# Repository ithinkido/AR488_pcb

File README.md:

# AR488_pcb
 Kicad Files for the AR488 GP-IB adapter with files for both the Pro MIcro and Nano MCU.

Silkcreen and solder mask to help with parts rotation. 

Files are avalible for single , 5x pannelization versions as well as 10x version which does not have mounting holes on the PCB. All designs fit in the 100x100mm size limit of most of the PSB manufactures.

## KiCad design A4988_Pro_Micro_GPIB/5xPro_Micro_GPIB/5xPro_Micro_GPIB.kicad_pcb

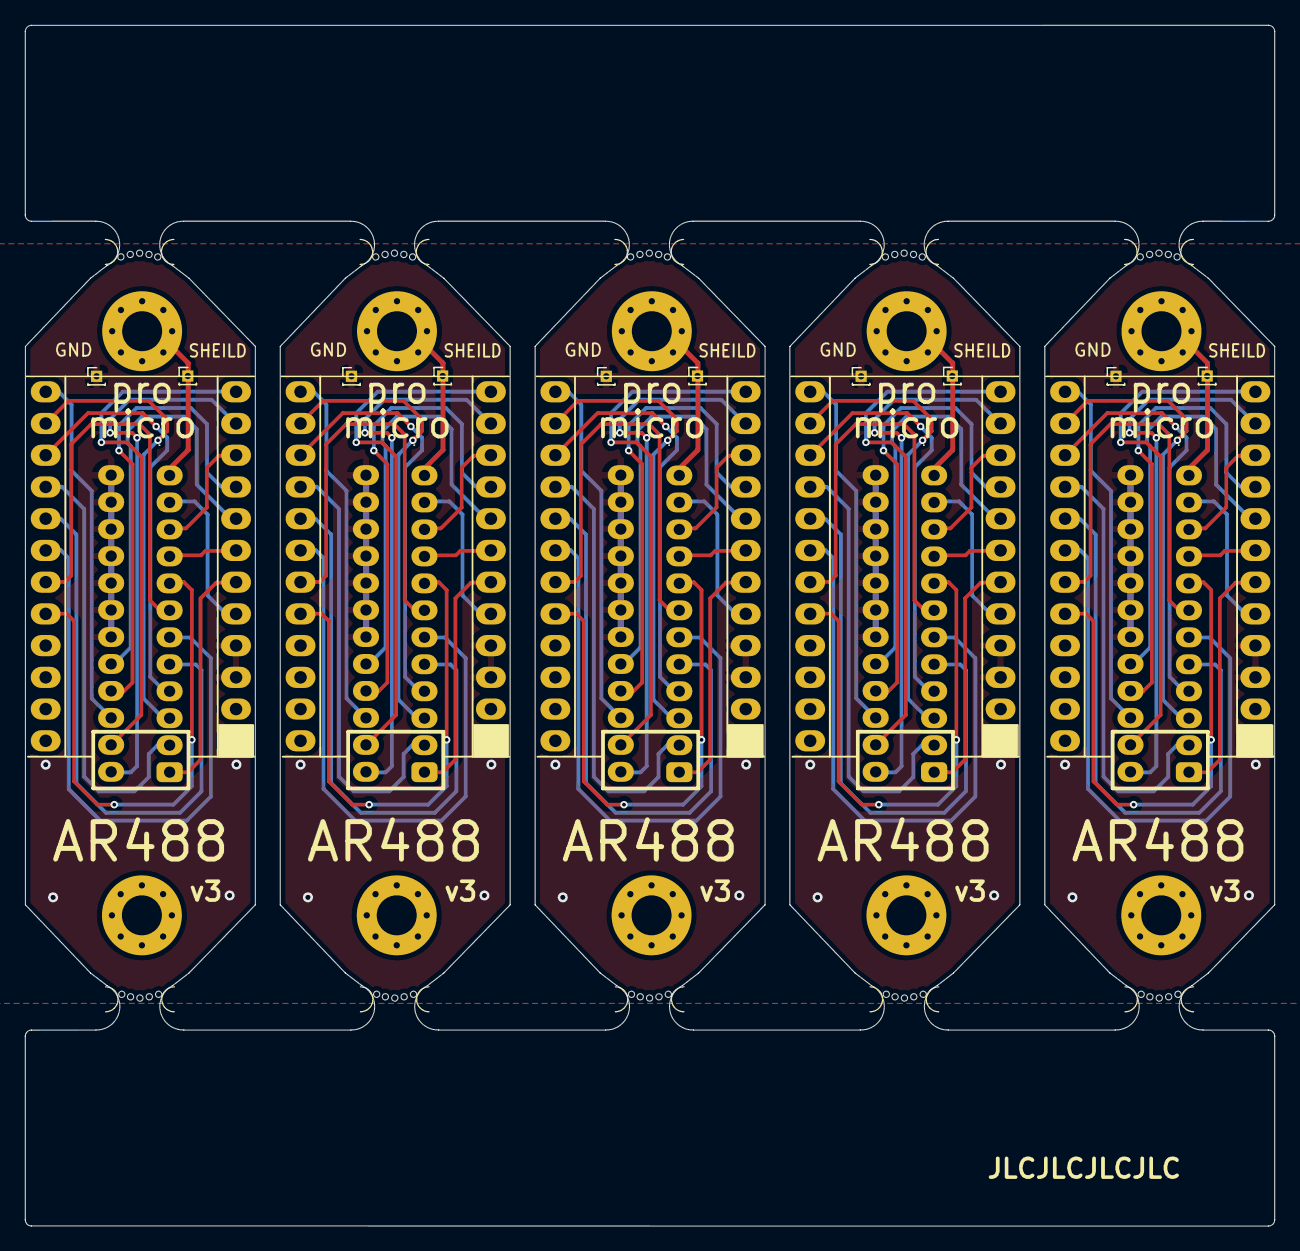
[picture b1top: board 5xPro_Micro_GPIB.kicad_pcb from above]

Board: 2 copper layers, 100.0 x 96.1 mm, 30 parts (0 on the bottom side), 18 nets.

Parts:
J1, J4, J7, J10, J13: Centronics_24p; Centronics24p
J2, J5, J8, J11, J14: GND; PinHeader_1x01_P1.00mm_Vertical
J3, J6, J9, J12, J15: SHIELD; PinHeader_1x01_P1.00mm_Vertical
U1, U2, U3, U4, U5: Pro_Micro_32u4; ProMicro-EnforcedTop
mouse-bite-2mm-slot, mouse-bite-2mm-slot1, mouse-bite-2mm-slot2, mouse-bite-2mm-slot3, mouse-bite-2mm-slot4, mouse-bite-2mm-slot5, mouse-bite-2mm-slot6, mouse-bite-2mm-slot7, mouse-bite-2mm-slot8, mouse-bite-2mm-slot#2: VAL**; mouse-bite-single-side_curve

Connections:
GND: J1.18, J1.19, J1.20, J1.21, J1.22, J1.23, J1.24, J2.1, J4.18, J4.19, J4.20, J4.21, J4.22, J4.23, J4.24, J5.1, J7.18, J7.19, J7.20, J7.21, J7.22, J7.23, J7.24, J8.1, J10.18, J10.19, J10.20, J10.21, J10.22, J10.23, J10.24, J11.1, J13.18, J13.19, J13.20, J13.21, J13.22, J13.23, J13.24, J14.1, U1.3 (GND), U1.4 (GND), U1.23 (GND), U2.3 (GND), U2.4 (GND), U2.23 (GND), U3.3 (GND), U3.4 (GND), U3.23 (GND), U4.3 (GND), U4.4 (GND), U4.23 (GND), U5.3 (GND), U5.4 (GND), U5.23 (GND)
GPIB 1 - DIO1: J1.1, J4.1, J7.1, J10.1, J13.1, U1.6 (D3), U2.6 (D3), U3.6 (D3), U4.6 (D3), U5.6 (D3)
GPIB 2 - DIO2: J1.2, J4.2, J7.2, J10.2, J13.2, U1.16 (D15), U2.16 (D15), U3.16 (D15), U4.16 (D15), U5.16 (D15)
GPIB 3 - DIO3: J1.3, J4.3, J7.3, J10.3, J13.3, U1.14 (D16), U2.14 (D16), U3.14 (D16), U4.14 (D16), U5.14 (D16)
GPIB 4 - DIO4: J1.4, J4.4, J7.4, J10.4, J13.4, U1.15 (D14), U2.15 (D14), U3.15 (D14), U4.15 (D14), U5.15 (D14)
GPIB 5 - EOI: J1.5, J4.5, J7.5, J10.5, J13.5, U1.17 (D18/A0), U2.17 (D18/A0), U3.17 (D18/A0), U4.17 (D18/A0), U5.17 (D18/A0)
GPIB 6 - DAV: J1.6, J4.6, J7.6, J10.6, J13.6, U1.18 (D19/A1), U2.18 (D19/A1), U3.18 (D19/A1), U4.18 (D19/A1), U5.18 (D19/A1)
GPIB 7-NRFD: J1.7, J4.7, J7.7, J10.7, J13.7, U1.19 (D20/A2), U2.19 (D20/A2), U3.19 (D20/A2), U4.19 (D20/A2), U5.19 (D20/A2)
GPIB 8 - NDAC: J1.8, J4.8, J7.8, J10.8, J13.8, U1.20 (D21/A3), U2.20 (D21/A3), U3.20 (D21/A3), U4.20 (D21/A3), U5.20 (D21/A3)
GPIB 9 - IFC: J1.9, J4.9, J7.9, J10.9, J13.9, U1.7 (D4/A6), U2.7 (D4/A6), U3.7 (D4/A6), U4.7 (D4/A6), U5.7 (D4/A6)
GPIB 10 - SRQ: J1.10, J4.10, J7.10, J10.10, J13.10, U1.10 (D7), U2.10 (D7), U3.10 (D7), U4.10 (D7), U5.10 (D7)
GPIB 11 - ATN: J1.11, J4.11, J7.11, J10.11, J13.11, U1.5 (D2), U2.5 (D2), U3.5 (D2), U4.5 (D2), U5.5 (D2)
GPIB 13 -DIO5: J1.13, J4.13, J7.13, J10.13, J13.13, U1.11 (D8/A8), U2.11 (D8/A8), U3.11 (D8/A8), U4.11 (D8/A8), U5.11 (D8/A8)
GPIB 14 - DIO6: J1.14, J4.14, J7.14, J10.14, J13.14, U1.12 (D9/A9), U2.12 (D9/A9), U3.12 (D9/A9), U4.12 (D9/A9), U5.12 (D9/A9)
GPIB 15 - DIO7: J1.15, J4.15, J7.15, J10.15, J13.15, U1.13 (D10/A10), U2.13 (D10/A10), U3.13 (D10/A10), U4.13 (D10/A10), U5.13 (D10/A10)
GPIB 16 - DIO8: J1.16, J4.16, J7.16, J10.16, J13.16, U1.9 (D6/A7), U2.9 (D6/A7), U3.9 (D6/A7), U4.9 (D6/A7), U5.9 (D6/A7)
GPIB 17 - REN: J1.17, J4.17, J7.17, J10.17, J13.17, U1.8 (D5), U2.8 (D5), U3.8 (D5), U4.8 (D5), U5.8 (D5)
SHIELD: J1.12, J3.1, J4.12, J6.1, J7.12, J9.1, J10.12, J12.1, J13.12, J15.1

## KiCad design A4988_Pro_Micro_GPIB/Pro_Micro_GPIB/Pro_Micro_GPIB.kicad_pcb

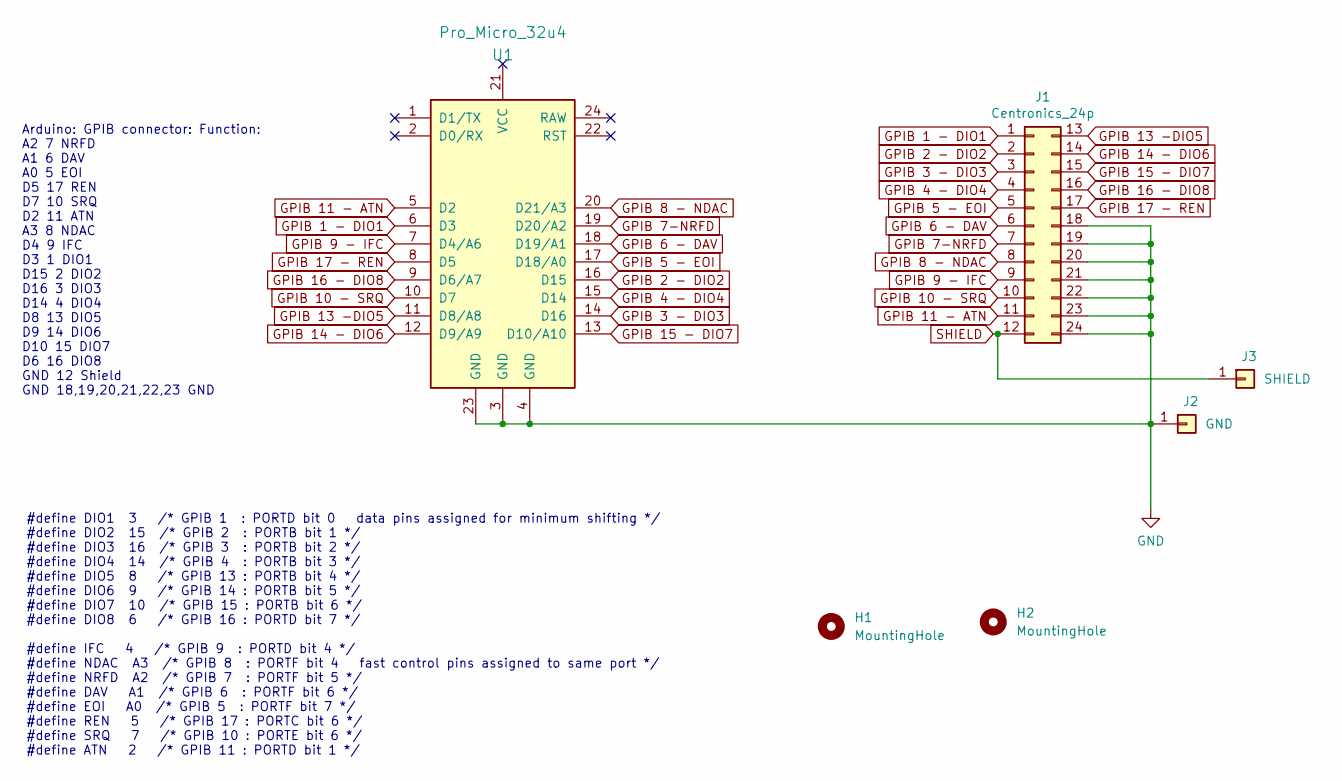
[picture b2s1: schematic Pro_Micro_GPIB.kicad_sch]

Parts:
H1, H2: MountingHole; MountingHole_3.2mm_M3_Pad_Via
J1: Centronics_24p; Centronics24p
J2: GND; PinHeader_1x01_P1.00mm_Vertical
J3: SHIELD; PinHeader_1x01_P1.00mm_Vertical
U1: Pro_Micro_32u4; Sparkfun_Pro_Micro

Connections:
GND: J1.18, J1.19, J1.20, J1.21, J1.22, J1.23, J1.24, J2.1, U1.3 (GND), U1.4 (GND), U1.23 (GND)
GPIB 1 - DIO1: J1.1, U1.6 (D3)
GPIB 2 - DIO2: J1.2, U1.16 (D15)
GPIB 3 - DIO3: J1.3, U1.14 (D16)
GPIB 4 - DIO4: J1.4, U1.15 (D14)
GPIB 5 - EOI: J1.5, U1.17 (D18/A0)
GPIB 6 - DAV: J1.6, U1.18 (D19/A1)
GPIB 7-NRFD: J1.7, U1.19 (D20/A2)
GPIB 8 - NDAC: J1.8, U1.20 (D21/A3)
GPIB 9 - IFC: J1.9, U1.7 (D4/A6)
GPIB 10 - SRQ: J1.10, U1.10 (D7)
GPIB 11 - ATN: J1.11, U1.5 (D2)
GPIB 13 -DIO5: J1.13, U1.11 (D8/A8)
GPIB 14 - DIO6: J1.14, U1.12 (D9/A9)
GPIB 15 - DIO7: J1.15, U1.13 (D10/A10)
GPIB 16 - DIO8: J1.16, U1.9 (D6/A7)
GPIB 17 - REN: J1.17, U1.8 (D5)
SHIELD: H1.1, J1.12, J3.1

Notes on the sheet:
#define DIO1 3 /* GPIB 1 : PORTD bit 0 data pins assigned for minimum shifting */ #define DIO2 15 /* GPIB 2 : PORTB bit 1 */ #define DIO3 16 /* GPIB 3 : PORTB bit 2 */ #define DIO4 14 /* GPIB 4 : PORTB bit 3 */ #define DIO5 8 /* GPIB 13 : PORTB bit 4 */ #define DIO6 9 /* GPIB 14 : PORTB bit 5 */ #d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
Arduino: GPIB connector: Function: A2 7 NRFD A1 6 DAV A0 5 EOI D5 17 REN D7 10 SRQ D2 11 ATN A3 8 NDAC D4 9 IFC D3 1 DIO1 D15 2 DIO2 D16 3 DIO3 D14 4 DIO4 D8 13 DIO5 D9 14 DIO6 D10 15 DIO7 D6 16 DIO8 GND 12 Shield GND 18,19,20,21,22,23 GND

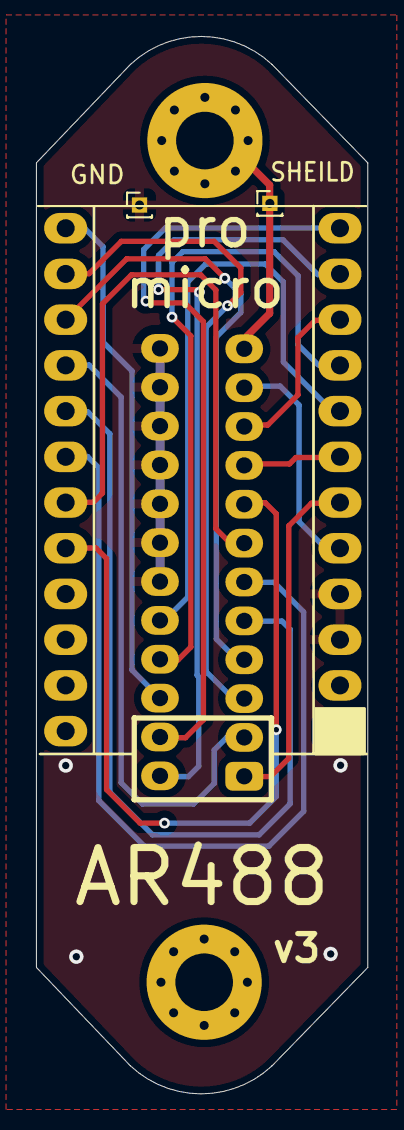
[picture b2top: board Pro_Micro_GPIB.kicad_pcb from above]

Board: 2 copper layers, 18.4 x 58.7 mm, 6 parts (0 on the bottom side), 18 nets.

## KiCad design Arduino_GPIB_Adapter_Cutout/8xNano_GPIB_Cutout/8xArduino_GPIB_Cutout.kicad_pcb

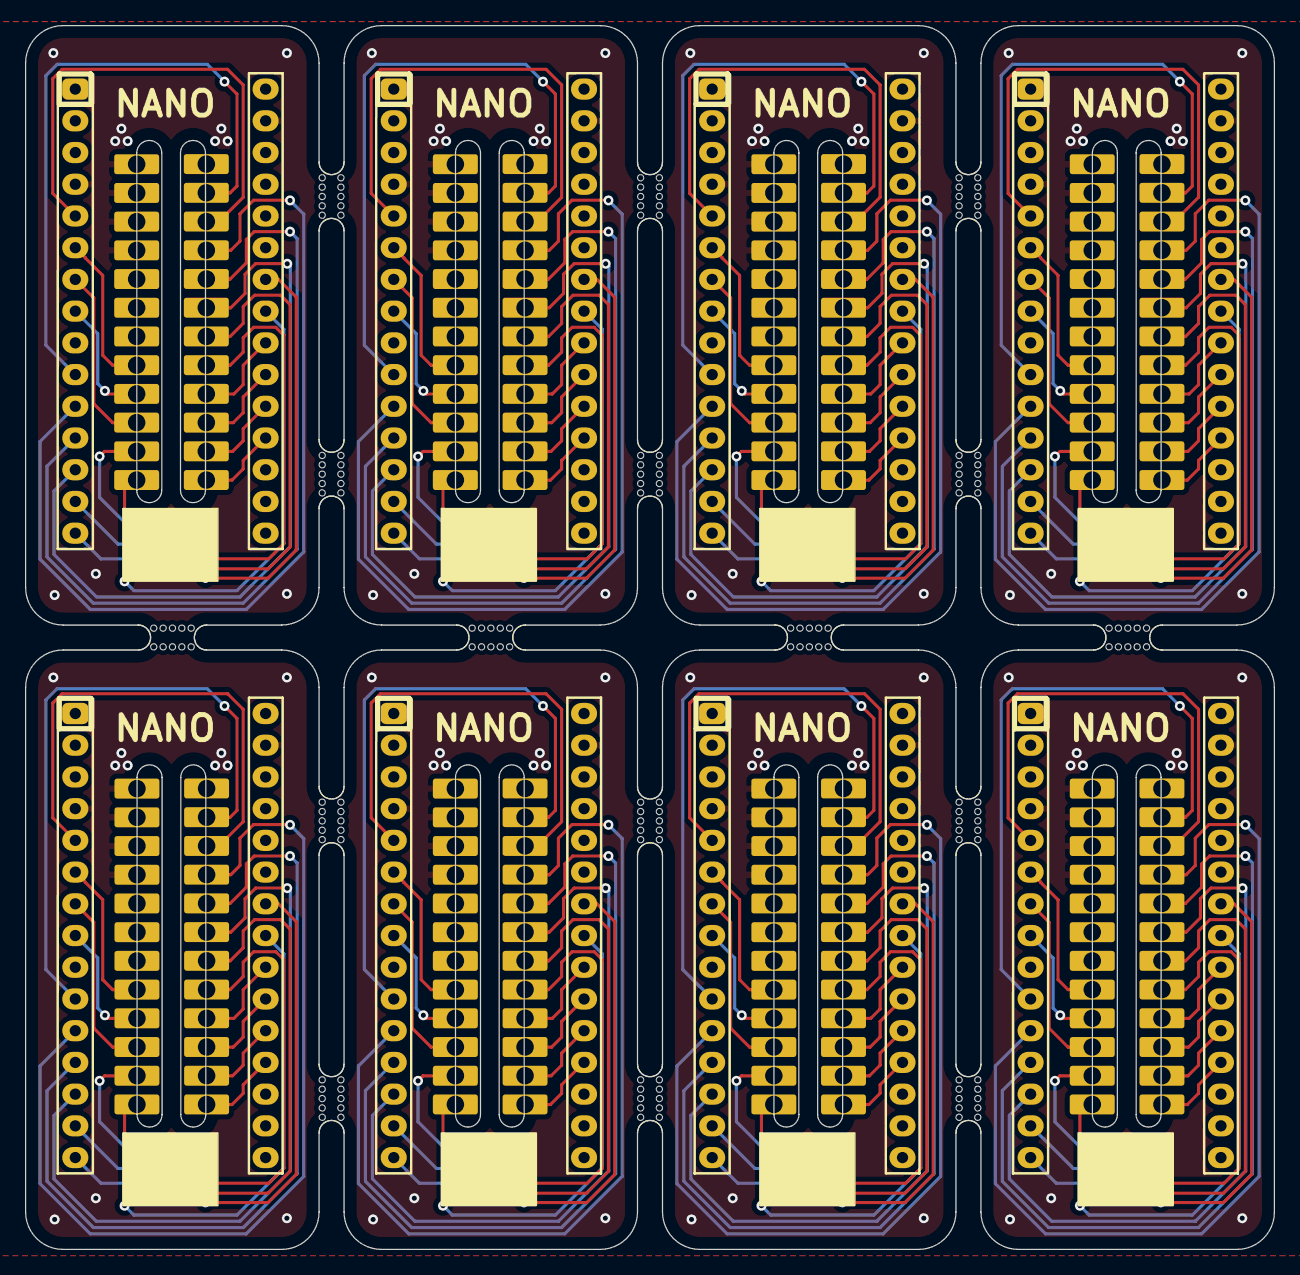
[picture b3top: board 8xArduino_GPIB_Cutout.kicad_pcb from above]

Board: 2 copper layers, 100.0 x 98.0 mm, 32 parts (0 on the bottom side), 29 nets.

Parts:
A1, A1#2, A2, A3, A4, A5, A6, A7: Arduino_Nano_v3.x; Arduino_Nano
P1, P1#2, P2, P3, P4, P5, P6, P7: GPIB; Centronics_24Pin_Castelated
mouse-bite-2mm-slot, mouse-bite-2mm-slot1, mouse-bite-2mm-slot2, mouse-bite-2mm-slot3, mouse-bite-2mm-slot4, mouse-bite-2mm-slot5, mouse-bite-2mm-slot6, mouse-bite-2mm-slot7, mouse-bite-2mm-slot8, mouse-bite-2mm-slot9, mouse-bite-2mm-slot10, mouse-bite-2mm-slot11, mouse-bite-2mm-slot12, mouse-bite-2mm-slot13, mouse-bite-2mm-slot#2, mouse-bite-2mm-slot#3: VAL**; mouse-bite

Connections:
/A0-DIO1: A1.19, A1#2.19, A2.19, A3.19, A4.19, A5.19, A6.19, A7.19, P1.1, P1#2.1, P2.1, P3.1, P4.1, P5.1, P6.1, P7.1
/A1-DIO2: A1.20, A1#2.20, A2.20, A3.20, A4.20, A5.20, A6.20, A7.20, P1.2, P1#2.2, P2.2, P3.2, P4.2, P5.2, P6.2, P7.2
/A2-DIO3: A1.21, A1#2.21, A2.21, A3.21, A4.21, A5.21, A6.21, A7.21, P1.3, P1#2.3, P2.3, P3.3, P4.3, P5.3, P6.3, P7.3
/A3-DIO4: A1.22, A1#2.22, A2.22, A3.22, A4.22, A5.22, A6.22, A7.22, P1.4, P1#2.4, P2.4, P3.4, P4.4, P5.4, P6.4, P7.4
/A4-DIO5: A1.23, A1#2.23, A2.23, A3.23, A4.23, A5.23, A6.23, A7.23, P1.13, P1#2.13, P2.13, P3.13, P4.13, P5.13, P6.13, P7.13
/A5-DIO6: A1.24, A1#2.24, A2.24, A3.24, A4.24, A5.24, A6.24, A7.24, P1.14, P1#2.14, P2.14, P3.14, P4.14, P5.14, P6.14, P7.14
/D2-SRQ: A1.5, A1#2.5, A2.5, A3.5, A4.5, A5.5, A6.5, A7.5, P1.10, P1#2.10, P2.10, P3.10, P4.10, P5.10, P6.10, P7.10
/D3-REN: A1.6, A1#2.6, A2.6, A3.6, A4.6, A5.6, A6.6, A7.6, P1.17, P1#2.17, P2.17, P3.17, P4.17, P5.17, P6.17, P7.17
/D4-DIO7: A1.7, A1#2.7, A2.7, A3.7, A4.7, A5.7, A6.7, A7.7, P1.15, P1#2.15, P2.15, P3.15, P4.15, P5.15, P6.15, P7.15
/D5-DIO8: A1.8, A1#2.8, A2.8, A3.8, A4.8, A5.8, A6.8, A7.8, P1.16, P1#2.16, P2.16, P3.16, P4.16, P5.16, P6.16, P7.16
/D7-ATN: A1.10, A1#2.10, A2.10, A3.10, A4.10, A5.10, A6.10, A7.10, P1.11, P1#2.11, P2.11, P3.11, P4.11, P5.11, P6.11, P7.11
/D8-IFC: A1.11, A1#2.11, A2.11, A3.11, A4.11, A5.11, A6.11, A7.11, P1.9, P1#2.9, P2.9, P3.9, P4.9, P5.9, P6.9, P7.9
/D9-NDAC: A1.12, A1#2.12, A2.12, A3.12, A4.12, A5.12, A6.12, A7.12, P1.8, P1#2.8, P2.8, P3.8, P4.8, P5.8, P6.8, P7.8
/D10-NRFD: A1.13, A1#2.13, A2.13, A3.13, A4.13, A5.13, A6.13, A7.13, P1.7, P1#2.7, P2.7, P3.7, P4.7, P5.7, P6.7, P7.7
/D11-DAV: A1.14, A1#2.14, A2.14, A3.14, A4.14, A5.14, A6.14, A7.14, P1.6, P1#2.6, P2.6, P3.6, P4.6, P5.6, P6.6, P7.6
/D12-EOI: A1.15, A1#2.15, A2.15, A3.15, A4.15, A5.15, A6.15, A7.15, P1.5, P1#2.5, P2.5, P3.5, P4.5, P5.5, P6.5, P7.5
GND: A1.4, A1.29, A1#2.4, A1#2.29, A2.4, A2.29, A3.4, A3.29, A4.4, A4.29, A5.4, A5.29, A6.4, A6.29, A7.4, A7.29, P1.18, P1.19, P1.20, P1.21, P1.22, P1.23, P1.24, P1#2.12, P1#2.18, P1#2.19, P1#2.20, P1#2.21, P1#2.22, P1#2.23, P1#2.24, P2.12, P2.18, P2.19, P2.20, P2.21, P2.22, P2.23, P2.24, P3.12, P3.18, P3.19, P3.20, P3.21, P3.22, P3.23, P3.24, P4.12, P4.18, P4.19, P4.20, P4.21, P4.22, P4.23, P4.24, P5.12, P5.18, P5.19, P5.20, P5.21, P5.22, P5.23, P5.24, P6.12, P6.18, P6.19, P6.20, P6.21, P6.22, P6.23, P6.24, P7.12, P7.18, P7.19, P7.20, P7.21, P7.22, P7.23, P7.24
unnamed: A1.1, A1#2.1, A2.1, A3.1, A4.1, A5.1, A6.1, A7.1
unnamed: A1.2, A1#2.2, A2.2, A3.2, A4.2, A5.2, A6.2, A7.2
unnamed: A1.3, A1#2.3, A2.3, A3.3, A4.3, A5.3, A6.3, A7.3
unnamed: A1.9, A1#2.9, A2.9, A3.9, A4.9, A5.9, A6.9, A7.9
unnamed: A1.16, A1#2.16, A2.16, A3.16, A4.16, A5.16, A6.16, A7.16
unnamed: A1.17, A1#2.17, A2.17, A3.17, A4.17, A5.17, A6.17, A7.17
unnamed: A1.18, A1#2.18, A2.18, A3.18, A4.18, A5.18, A6.18, A7.18
unnamed: A1.25, A1#2.25, A2.25, A3.25, A4.25, A5.25, A6.25, A7.25
unnamed: A1.26, A1#2.26, A2.26, A3.26, A4.26, A5.26, A6.26, A7.26
unnamed: A1.27, A1#2.27, A2.27, A3.27, A4.27, A5.27, A6.27, A7.27
unnamed: A1.28, A1#2.28, A2.28, A3.28, A4.28, A5.28, A6.28, A7.28
unnamed: A1.30, A1#2.30, A2.30, A3.30, A4.30, A5.30, A6.30, A7.30

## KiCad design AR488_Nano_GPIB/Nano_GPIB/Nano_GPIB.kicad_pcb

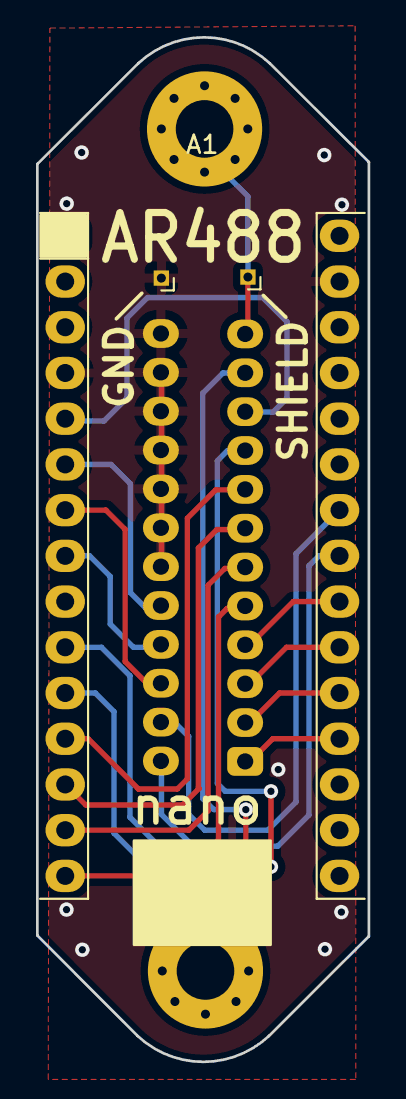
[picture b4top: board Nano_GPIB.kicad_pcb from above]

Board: 2 copper layers, 18.4 x 56.9 mm, 4 parts (0 on the bottom side), 18 nets.

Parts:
A1: Arduino_Nano_v3.x; Arduino_Nano
J1: Conn_02x12_Top_Bottom; Centronics24p
J2: GND; PinHeader_1x01_P1.00mm_Vertical
J3: SHIELD; PinHeader_1x01_P1.00mm_Vertical

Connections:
GND: A1.4 (GND), A1.29 (GND), J1.18, J1.19, J1.20, J1.21, J1.22, J1.23, J1.24, J2.1
GPIB 1 - DIO1: A1.19 (A0), J1.1
GPIB 2 - DIO2: A1.20 (A1), J1.2
GPIB 3 - DIO3: A1.21 (A2), J1.3
GPIB 4 - DIO4: A1.22 (A3), J1.4
GPIB 5 - EOI: A1.15 (D12), J1.5
GPIB 6 - DAV: A1.14 (D11), J1.6
GPIB 7 - NRFD: A1.13 (D10), J1.7
GPIB 8 - NDAC: A1.12 (D9), J1.8
GPIB 9 - IFC: A1.11 (D8), J1.9
GPIB 10 - SRQ: A1.5 (D2), J1.10
GPIB 11 - ATN: A1.10 (D7), J1.11
GPIB 13 - GIO5: A1.23 (A4), J1.13
GPIB 14 - DIO6: A1.24 (A5), J1.14
GPIB 15 - DIO7: A1.7 (D4), J1.15
GPIB 16 - DIO8: A1.8 (D5), J1.16
GPIB 17 - REN: A1.6 (D3), J1.17
unnamed: J1.12, J3.1

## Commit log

2022-03-27 upload
    Initial commit
    upload files
2022-07-05 nano
